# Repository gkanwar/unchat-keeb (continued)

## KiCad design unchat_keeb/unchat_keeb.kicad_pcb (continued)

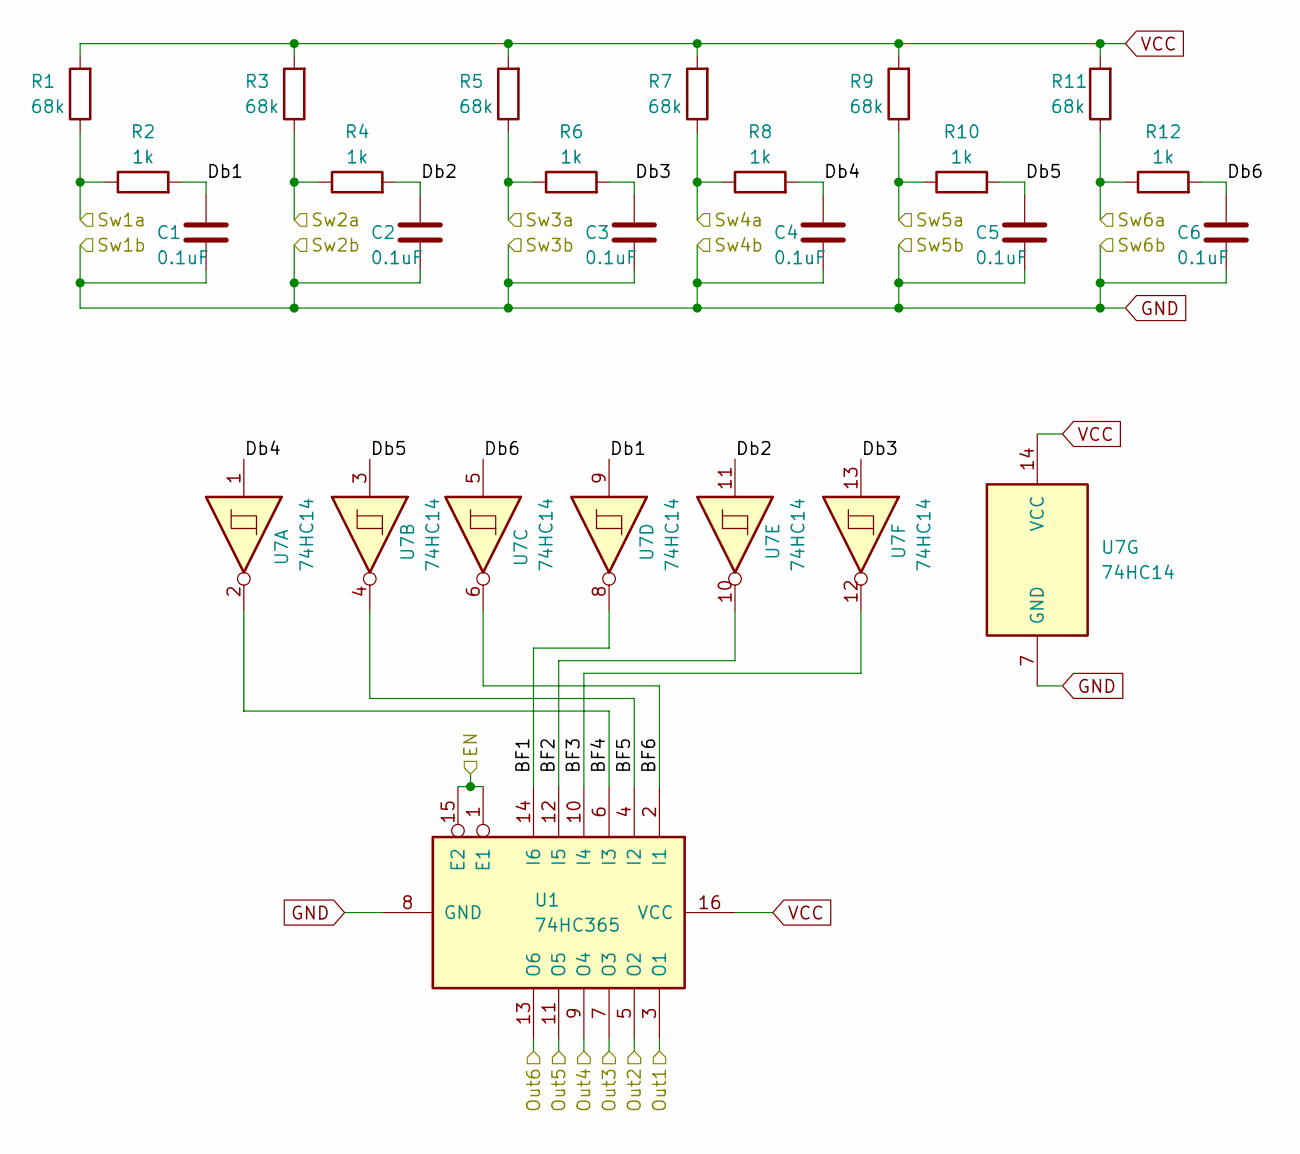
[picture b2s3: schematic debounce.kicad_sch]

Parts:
C1, C2, C3, C4, C5, C6: 0.1uF; C_0805_2012Metric
R1, R3, R5, R7, R9, R11: 68k; R_0805_2012Metric
R2, R4, R6, R8, R10, R12: 1k; R_0805_2012Metric
U1: 74HC365; TSSOP-16_4.4x5mm_P0.65mm
U7: 74HC14; TSSOP-14_4.4x5mm_P0.65mm

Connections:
/BUS1: U1.3 (O1); also elsewhere on the board
/BUS2: U1.5 (O2); also elsewhere on the board
/BUS3: U1.7 (O3); also elsewhere on the board
/BUS4: U1.9 (O4); also elsewhere on the board
/BUS5: U1.11 (O5); also elsewhere on the board
/BUS6: U1.13 (O6); also elsewhere on the board
/Left Debounce 1-6/BF1: U1.14 (I6), U7.8
/Left Debounce 1-6/BF2: U1.12 (I5), U7.10
/Left Debounce 1-6/BF3: U1.10 (I4), U7.12
/Left Debounce 1-6/BF4: U1.6 (I3), U7.2
/Left Debounce 1-6/BF5: U1.4 (I2), U7.4
/Left Debounce 1-6/BF6: U1.2 (I1), U7.6
/Left Debounce 1-6/Db1: C1.1, R2.2, U7.9
/Left Debounce 1-6/Db2: C2.1, R4.2, U7.11
/Left Debounce 1-6/Db4: C4.1, R8.2, U7.1
/Left Debounce 1-6/Db5: C5.1, R10.2, U7.3
/Left Debounce 1-6/Db6: C6.1, R12.2, U7.5
/S1a: R1.1, R2.1; also elsewhere on the board
/S2a: R3.1, R4.1; also elsewhere on the board
/S3a: R5.1, R6.1; also elsewhere on the board
/S4a: R7.1, R8.1; also elsewhere on the board
/S5a: R9.1, R10.1; also elsewhere on the board
/S6a: R11.1, R12.1; also elsewhere on the board
GND: C1.2, C2.2, C3.2, C4.2, C5.2, C6.2, U1.8 (GND), U7.7 (GND); also elsewhere on the board
U1_EN: U1.1 (E1), U1.15 (E2); also elsewhere on the board

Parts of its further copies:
C7, C8, C9, C10, C11, C12, C13, C14, C15, C16, C17, C18, C19, C20, C21, C22, C23, C24, C25, C26, C27, C28, C29, C30, C31, C32, C33, C34, C35, C36, C37, C38, C39, C40, C41, C42: 0.1uF; C_0805_2012Metric
R13, R15, R17, R19, R21, R23, R25, R27, R29, R31, R33, R35, R37, R39, R41, R43, R45, R47, R49, R51, R53, R55, R57, R59, R61, R63, R65, R67, R69, R71, R117, R118, R119, R120, R121, R122: 68k; R_0805_2012Metric
R14, R16, R18, R20, R22, R24, R26, R28, R30, R32, R34, R36, R38, R40, R42, R44, R46, R48, R50, R52, R54, R56, R58, R60, R62, R64, R66, R68, R70, R72, R123, R124, R125, R126, R127, R128: 1k; R_0805_2012Metric
U2, U3, U4, U5, U6, U66: 74HC365; TSSOP-16_4.4x5mm_P0.65mm
U8, U9, U10, U11, U12, U25: 74HC14; TSSOP-14_4.4x5mm_P0.65mm

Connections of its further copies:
/BUS1: U2.3 (O1), U3.3 (O1), U4.3 (O1), U5.3 (O1), U6.3 (O1), U66.3 (O1); also elsewhere on the board
/BUS2: U2.5 (O2), U3.5 (O2), U4.5 (O2), U5.5 (O2), U6.5 (O2), U66.5 (O2); also elsewhere on the board
/BUS3: U2.7 (O3), U3.7 (O3), U4.7 (O3), U5.7 (O3), U6.7 (O3), U66.7 (O3); also elsewhere on the board
/BUS4: U2.9 (O4), U3.9 (O4), U4.9 (O4), U5.9 (O4), U6.9 (O4), U66.9 (O4); also elsewhere on the board
/BUS5: U2.11 (O5), U3.11 (O5), U4.11 (O5), U5.11 (O5), U6.11 (O5), U66.11 (O5); also elsewhere on the board
/BUS6: U2.13 (O6), U3.13 (O6), U4.13 (O6), U5.13 (O6), U6.13 (O6), U66.13 (O6); also elsewhere on the board
/Left Debounce 7-12/BF1: U2.14 (I6), U8.8
/Left Debounce 7-12/BF2: U2.12 (I5), U8.10
/Left Debounce 7-12/BF3: U2.10 (I4), U8.12
/Left Debounce 7-12/BF4: U2.6 (I3), U8.2
/Left Debounce 7-12/BF5: U2.4 (I2), U8.4
/Left Debounce 7-12/BF6: U2.2 (I1), U8.6
/Left Debounce 7-12/Db1: C7.1, R14.2, U8.9
/Left Debounce 7-12/Db2: C8.1, R16.2, U8.11
/Left Debounce 7-12/Db3: C9.1, R18.2, U8.13
/Left Debounce 7-12/Db4: C10.1, R20.2, U8.1
/Left Debounce 7-12/Db5: C11.1, R22.2, U8.3
/Left Debounce 7-12/Db6: C12.1, R24.2, U8.5
/Left Debounce 13-18/BF1: U3.14 (I6), U9.8
/Left Debounce 13-18/BF2: U3.12 (I5), U9.10
/Left Debounce 13-18/BF3: U3.10 (I4), U9.12
/Left Debounce 13-18/BF4: U3.6 (I3), U9.2
/Left Debounce 13-18/BF5: U3.4 (I2), U9.4
/Left Debounce 13-18/BF6: U3.2 (I1), U9.6
/Left Debounce 13-18/Db1: C13.1, R26.2, U9.9
/Left Debounce 13-18/Db2: C14.1, R28.2, U9.11
/Left Debounce 13-18/Db3: C15.1, R30.2, U9.13
/Left Debounce 13-18/Db4: C16.1, R32.2, U9.1
/Left Debounce 13-18/Db5: C17.1, R34.2, U9.3
/Left Debounce 13-18/Db6: C18.1, R36.2, U9.5
/Right Debounce 1-7/BF1: U4.14 (I6), U10.8
/Right Debounce 1-7/BF2: U4.12 (I5), U10.10
/Right Debounce 1-7/BF3: U4.10 (I4), U10.12
/Right Debounce 1-7/BF4: U4.6 (I3), U10.2
/Right Debounce 1-7/BF5: U4.4 (I2), U10.4
/Right Debounce 1-7/BF6: U4.2 (I1), U10.6
/Right Debounce 1-7/Db1: C19.1, R38.2, U10.9
/Right Debounce 1-7/Db2: C20.1, R40.2, U10.11
/Right Debounce 1-7/Db3: C21.1, R42.2, U10.13
/Right Debounce 1-7/Db4: C22.1, R44.2, U10.1
/Right Debounce 1-7/Db5: C23.1, R46.2, U10.3
/Right Debounce 1-7/Db6: C24.1, R48.2, U10.5
/Right Debounce 7-13/BF1: U5.14 (I6), U11.8
/Right Debounce 7-13/BF2: U5.12 (I5), U11.10
/Right Debounce 7-13/BF3: U5.10 (I4), U11.12
/Right Debounce 7-13/BF4: U5.6 (I3), U11.2
/Right Debounce 7-13/BF5: U5.4 (I2), U11.4
/Right Debounce 7-13/BF6: U5.2 (I1), U11.6
/Right Debounce 7-13/Db1: C25.1, R50.2, U11.9
/Right Debounce 7-13/Db2: C26.1, R52.2, U11.11
/Right Debounce 7-13/Db3: C27.1, R54.2, U11.13
/Right Debounce 7-13/Db4: C28.1, R56.2, U11.1
/Right Debounce 7-13/Db5: C29.1, R58.2, U11.3
/Right Debounce 7-13/Db6: C30.1, R60.2, U11.5
/Right Debounce 13-19/BF1: U6.14 (I6), U12.8
/Right Debounce 13-19/BF2: U6.12 (I5), U12.10
/Right Debounce 13-19/BF3: U6.10 (I4), U12.12
/Right Debounce 13-19/BF4: U6.6 (I3), U12.2
/Right Debounce 13-19/BF5: U6.4 (I2), U12.4
/Right Debounce 13-19/BF6: U6.2 (I1), U12.6
/Right Debounce 13-19/Db1: C31.1, R62.2, U12.9
/Right Debounce 13-19/Db2: C32.1, R64.2, U12.11
/Right Debounce 13-19/Db3: C33.1, R66.2, U12.13
/Right Debounce 13-19/Db4: C34.1, R68.2, U12.1
/Right Debounce 13-19/Db5: C35.1, R70.2, U12.3
/Right Debounce 13-19/Db6: C36.1, R72.2, U12.5
/S7a: R13.1, R14.1; also elsewhere on the board
/S8a: R15.1, R16.1; also elsewhere on the board
/S9a: R17.1, R18.1; also elsewhere on the board
/S10a: R19.1, R20.1; also elsewhere on the board
/S11a: R21.1, R22.1; also elsewhere on the board
/S12a: R23.1, R24.1; also elsewhere on the board
/S13a: R25.1, R26.1; also elsewhere on the board
/S14a: R27.1, R28.1; also elsewhere on the board
/S15a: R29.1, R30.1; also elsewhere on the board
/S16a: R31.1, R32.1; also elsewhere on the board
/S17a: R33.1, R34.1; also elsewhere on the board
/S18a: R35.1, R36.1; also elsewhere on the board
/S19a: R117.1, R123.1; also elsewhere on the board
/S20a: R118.1, R124.1; also elsewhere on the board
/S21a: R119.1, R125.1; also elsewhere on the board
/S22a: R37.1, R38.1; also elsewhere on the board
/S23a: R39.1, R40.1; also elsewhere on the board
/S24a: R41.1, R42.1; also elsewhere on the board
/S25a: R43.1, R44.1; also elsewhere on the board
/S26a: R45.1, R46.1; also elsewhere on the board
/S27a: R47.1, R48.1; also elsewhere on the board
/S28a: R49.1, R50.1; also elsewhere on the board
/S29a: R51.1, R52.1; also elsewhere on the board
/S30a: R53.1, R54.1; also elsewhere on the board
/S31a: R55.1, R56.1; also elsewhere on the board
/S32a: R57.1, R58.1; also elsewhere on the board
/S33a: R59.1, R60.1; also elsewhere on the board
/S34a: R61.1, R62.1; also elsewhere on the board
/S35a: R63.1, R64.1; also elsewhere on the board
/S36a: R65.1, R66.1; also elsewhere on the board
/S37a: R67.1, R68.1; also elsewhere on the board
/S38a: R69.1, R70.1; also elsewhere on the board
/S39a: R71.1, R72.1; also elsewhere on the board
/S40a: R120.1, R126.1; also elsewhere on the board
/S41a: R121.1, R127.1; also elsewhere on the board
/S42a: R122.1, R128.1; also elsewhere on the board
/Thumb Debounce/BF1: U25.8, U66.14 (I6)
/Thumb Debounce/BF2: U25.10, U66.12 (I5)
/Thumb Debounce/BF3: U25.12, U66.10 (I4)
/Thumb Debounce/BF4: U25.2, U66.6 (I3)
/Thumb Debounce/BF5: U25.4, U66.4 (I2)
/Thumb Debounce/BF6: U25.6, U66.2 (I1)
/Thumb Debounce/Db1: C37.1, R123.2, U25.9
/Thumb Debounce/Db2: C38.1, R124.2, U25.11
/Thumb Debounce/Db3: C39.1, R125.2, U25.13
/Thumb Debounce/Db4: C40.1, R126.2, U25.1
/Thumb Debounce/Db5: C41.1, R127.2, U25.3
/Thumb Debounce/Db6: C42.1, R128.2, U25.5
GND: C7.2, C8.2, C9.2, C10.2, C11.2, C12.2, C13.2, C14.2, C15.2, C16.2, C17.2, C18.2, C19.2, C20.2, C21.2, C22.2, C23.2, C24.2, C25.2, C26.2, C27.2, C28.2, C29.2, C30.2, C31.2, C32.2, C33.2, C34.2, C35.2, C36.2, C37.2, C38.2, C39.2, C40.2, C41.2, C42.2, U2.8 (GND), U3.8 (GND), U4.8 (GND), U5.8 (GND), U6.8 (GND), U8.7 (GND), U9.7 (GND), U10.7 (GND), U11.7 (GND), U12.7 (GND), U25.7 (GND), U66.8 (GND); also elsewhere on the board
U2_EN: U2.1 (E1), U2.15 (E2); also elsewhere on the board
U3_EN: U3.1 (E1), U3.15 (E2); also elsewhere on the board
U4_EN: U4.1 (E1), U4.15 (E2); also elsewhere on the board
U5_EN: U5.1 (E1), U5.15 (E2); also elsewhere on the board
U6_EN: U6.1 (E1), U6.15 (E2); also elsewhere on the board
U66_EN: U66.1 (E1), U66.15 (E2); also elsewhere on the board

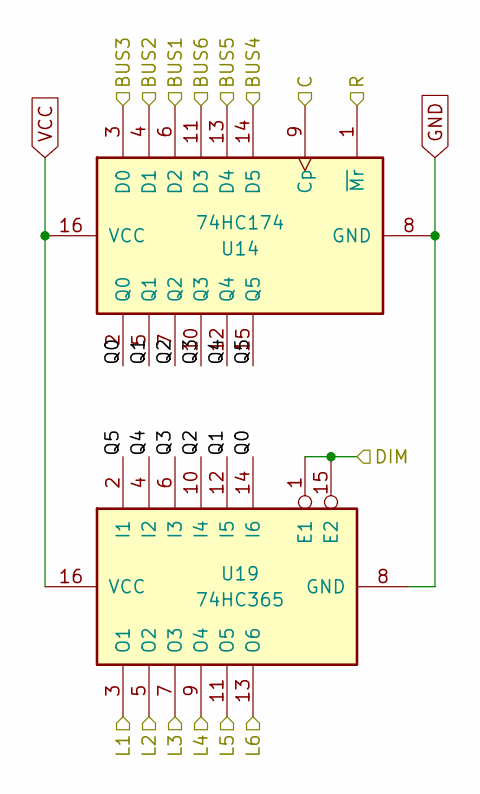
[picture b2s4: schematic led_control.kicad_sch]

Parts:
U14: 74HC174; TSSOP-16_4.4x5mm_P0.65mm
U19: 74HC365; TSSOP-16_4.4x5mm_P0.65mm

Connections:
/BUS1: U14.6 (D2); also elsewhere on the board
/BUS2: U14.4 (D1); also elsewhere on the board
/BUS3: U14.3 (D0); also elsewhere on the board
/BUS4: U14.14 (D5); also elsewhere on the board
/BUS5: U14.13 (D4); also elsewhere on the board
/BUS6: U14.11 (D3); also elsewhere on the board
/LL2: U19.5 (O2); also elsewhere on the board
/LL3: U19.7 (O3); also elsewhere on the board
/LL4: U19.9 (O4); also elsewhere on the board
/LL5: U19.11 (O5); also elsewhere on the board
/LL6: U19.13 (O6); also elsewhere on the board
GND: U14.8 (GND), U19.8 (GND); also elsewhere on the board
LED_DIM: U19.1 (E1), U19.15 (E2); also elsewhere on the board
LED_RST: U14.1 (~Mr); also elsewhere on the board
U14_CLK: U14.9 (Cp); also elsewhere on the board

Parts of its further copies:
U13, U15, U16, U17, U18, U26: 74HC174; TSSOP-16_4.4x5mm_P0.65mm
U20, U21, U22, U23, U24, U27: 74HC365; TSSOP-16_4.4x5mm_P0.65mm

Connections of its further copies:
/BUS1: U13.6 (D2), U15.6 (D2), U16.6 (D2), U17.6 (D2), U18.6 (D2), U26.6 (D2); also elsewhere on the board
/BUS2: U13.4 (D1), U15.4 (D1), U16.4 (D1), U17.4 (D1), U18.4 (D1), U26.4 (D1); also elsewhere on the board
/BUS3: U13.3 (D0), U15.3 (D0), U16.3 (D0), U17.3 (D0), U18.3 (D0), U26.3 (D0); also elsewhere on the board
/BUS4: U13.14 (D5), U15.14 (D5), U16.14 (D5), U17.14 (D5), U18.14 (D5), U26.14 (D5); also elsewhere on the board
/BUS5: U13.13 (D4), U15.13 (D4), U16.13 (D4), U17.13 (D4), U18.13 (D4), U26.13 (D4); also elsewhere on the board
/BUS6: U13.11 (D3), U15.11 (D3), U16.11 (D3), U17.11 (D3), U18.11 (D3), U26.11 (D3); also elsewhere on the board
/LL7: U20.3 (O1); also elsewhere on the board
/LL8: U20.5 (O2); also elsewhere on the board
/LL9: U20.7 (O3); also elsewhere on the board
/LL10: U20.9 (O4); also elsewhere on the board
/LL11: U20.11 (O5); also elsewhere on the board
/LL12: U20.13 (O6); also elsewhere on the board
/LL13: U21.3 (O1); also elsewhere on the board
/LL14: U21.5 (O2); also elsewhere on the board
/LL15: U21.7 (O3); also elsewhere on the board
/LL16: U21.9 (O4); also elsewhere on the board
/LL17: U21.11 (O5); also elsewhere on the board
/LL18: U21.13 (O6); also elsewhere on the board
/LL19: U27.3 (O1); also elsewhere on the board
/LL20: U27.5 (O2); also elsewhere on the board
/LL21: U27.7 (O3); also elsewhere on the board
/LR1: U22.3 (O1); also elsewhere on the board
/LR2: U22.5 (O2); also elsewhere on the board
/LR3: U22.7 (O3); also elsewhere on the board
/LR4: U22.9 (O4); also elsewhere on the board
/LR5: U22.11 (O5); also elsewhere on the board
/LR6: U22.13 (O6); also elsewhere on the board
/LR7: U23.3 (O1); also elsewhere on the board
/LR8: U23.5 (O2); also elsewhere on the board
/LR9: U23.7 (O3); also elsewhere on the board
/LR10: U23.9 (O4); also elsewhere on the board
/LR11: U23.11 (O5); also elsewhere on the board
/LR12: U23.13 (O6); also elsewhere on the board
/LR13: U24.3 (O1); also elsewhere on the board
/LR14: U24.5 (O2); also elsewhere on the board
/LR15: U24.7 (O3); also elsewhere on the board
/LR16: U24.9 (O4); also elsewhere on the board
/LR17: U24.11 (O5); also elsewhere on the board
/LR18: U24.13 (O6); also elsewhere on the board
/LR19: U27.9 (O4); also elsewhere on the board
/LR20: U27.11 (O5); also elsewhere on the board
/LR21: U27.13 (O6); also elsewhere on the board
/Left LED Control 13-18/Q0: U15.2 (Q0), U21.14 (I6)
/Left LED Control 13-18/Q1: U15.5 (Q1), U21.12 (I5)
/Left LED Control 13-18/Q2: U15.7 (Q2), U21.10 (I4)
/Left LED Control 13-18/Q3: U15.10 (Q3), U21.6 (I3)
/Left LED Control 13-18/Q4: U15.12 (Q4), U21.4 (I2)
/Left LED Control 13-18/Q5: U15.15 (Q5), U21.2 (I1)
/Right LED Control 1-6/Q0: U16.2 (Q0), U22.14 (I6)
/Right LED Control 1-6/Q1: U16.5 (Q1), U22.12 (I5)
/Right LED Control 1-6/Q2: U16.7 (Q2), U22.10 (I4)
/Right LED Control 1-6/Q3: U16.10 (Q3), U22.6 (I3)
/Right LED Control 1-6/Q4: U16.12 (Q4), U22.4 (I2)
/Right LED Control 1-6/Q5: U16.15 (Q5), U22.2 (I1)
/Right LED Control 7-12/Q0: U17.2 (Q0), U23.14 (I6)
/Right LED Control 7-12/Q1: U17.5 (Q1), U23.12 (I5)
/Right LED Control 7-12/Q2: U17.7 (Q2), U23.10 (I4)
/Right LED Control 7-12/Q3: U17.10 (Q3), U23.6 (I3)
/Right LED Control 7-12/Q4: U17.12 (Q4), U23.4 (I2)
/Right LED Control 7-12/Q5: U17.15 (Q5), U23.2 (I1)
/Right LED Control 13-18/Q0: U18.2 (Q0), U24.14 (I6)
/Right LED Control 13-18/Q1: U18.5 (Q1), U24.12 (I5)
/Right LED Control 13-18/Q2: U18.7 (Q2), U24.10 (I4)
/Right LED Control 13-18/Q3: U18.10 (Q3), U24.6 (I3)
/Right LED Control 13-18/Q4: U18.12 (Q4), U24.4 (I2)
/Right LED Control 13-18/Q5: U18.15 (Q5), U24.2 (I1)
/Thumb LED Control/Q0: U26.2 (Q0), U27.14 (I6)
/Thumb LED Control/Q1: U26.5 (Q1), U27.12 (I5)
/Thumb LED Control/Q2: U26.7 (Q2), U27.10 (I4)
/Thumb LED Control/Q3: U26.10 (Q3), U27.6 (I3)
/Thumb LED Control/Q4: U26.12 (Q4), U27.4 (I2)
/Thumb LED Control/Q5: U26.15 (Q5), U27.2 (I1)
GND: U13.8 (GND), U15.8 (GND), U16.8 (GND), U17.8 (GND), U18.8 (GND), U20.8 (GND), U21.8 (GND), U22.8 (GND), U23.8 (GND), U24.8 (GND), U26.8 (GND), U27.8 (GND); also elsewhere on the board
LED_DIM: U20.1 (E1), U20.15 (E2), U21.1 (E1), U21.15 (E2), U22.1 (E1), U22.15 (E2), U23.1 (E1), U23.15 (E2), U24.1 (E1), U24.15 (E2), U27.1 (E1), U27.15 (E2); also elsewhere on the board
LED_RST: U13.1 (~Mr), U15.1 (~Mr), U16.1 (~Mr), U17.1 (~Mr), U18.1 (~Mr), U26.1 (~Mr); also elsewhere on the board
U13_CLK: U13.9 (Cp); also elsewhere on the board
U15_CLK: U15.9 (Cp); also elsewhere on the board
U16_CLK: U16.9 (Cp); also elsewhere on the board
U17_CLK: U17.9 (Cp); also elsewhere on the board
U18_CLK: U18.9 (Cp); also elsewhere on the board
U26_CLK: U26.9 (Cp); also elsewhere on the board

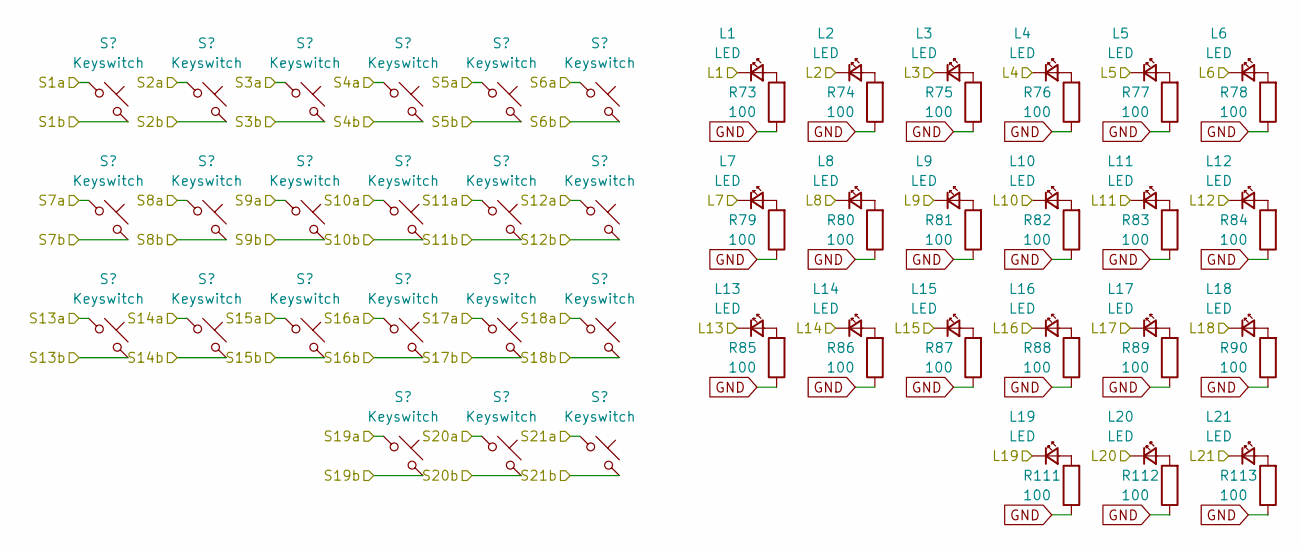
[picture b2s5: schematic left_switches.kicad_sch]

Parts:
L1, L2, L3, L4, L5, L6, L7, L8, L9, L10, L11, L12, L13, L14, L15, L16, L17, L18, L19, L20, L21: LED; LED_0603_1608Metric
R73, R74, R75, R76, R77, R78, R79, R80, R81, R82, R83, R84, R85, R86, R87, R88, R89, R90, R111, R112, R113: 100; R_0805_2012Metric
S1, S2, S3, S4, S5, S6, S7, S8, S9, S10, S11, S12, S13, S14, S15, S16, S17, S18, S19: Keyswitch; Choc_V1_LED_1.00u
S20, S21: Keyswitch; Choc_V1_LED_1.50u_90deg

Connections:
/LL2: L2.1 (K); also elsewhere on the board
/LL3: L3.1 (K); also elsewhere on the board
/LL4: L4.1 (K); also elsewhere on the board
/LL5: L5.1 (K); also elsewhere on the board
/LL6: L6.1 (K); also elsewhere on the board
/LL7: L7.1 (K); also elsewhere on the board
/LL8: L8.1 (K); also elsewhere on the board
/LL9: L9.1 (K); also elsewhere on the board
/LL10: L10.1 (K); also elsewhere on the board
/LL11: L11.1 (K); also elsewhere on the board
/LL12: L12.1 (K); also elsewhere on the board
/LL13: L13.1 (K); also elsewhere on the board
/LL14: L14.1 (K); also elsewhere on the board
/LL15: L15.1 (K); also elsewhere on the board
/LL16: L16.1 (K); also elsewhere on the board
/LL17: L17.1 (K); also elsewhere on the board
/LL18: L18.1 (K); also elsewhere on the board
/LL19: L19.1 (K); also elsewhere on the board
/LL20: L20.1 (K); also elsewhere on the board
/LL21: L21.1 (K); also elsewhere on the board
/S1a: S1.1; also elsewhere on the board
/S2a: S2.1; also elsewhere on the board
/S3a: S3.1; also elsewhere on the board
/S4a: S4.1; also elsewhere on the board
/S5a: S5.1; also elsewhere on the board
/S6a: S6.1; also elsewhere on the board
/S7a: S7.1; also elsewhere on the board
/S8a: S8.1; also elsewhere on the board
/S9a: S9.1; also elsewhere on the board
/S10a: S10.1; also elsewhere on the board
/S11a: S11.1; also elsewhere on the board
/S12a: S12.1; also elsewhere on the board
/S13a: S13.1; also elsewhere on the board
/S14a: S14.1; also elsewhere on the board
/S15a: S15.1; also elsewhere on the board
/S16a: S16.1; also elsewhere on the board
/S17a: S17.1; also elsewhere on the board
/S18a: S18.1; also elsewhere on the board
/S19a: S19.1; also elsewhere on the board
/S20a: S20.1; also elsewhere on the board
/S21a: S21.1; also elsewhere on the board
GND: R73.1, R74.1, R75.1, R76.1, R77.1, R78.1, R79.1, R80.1, R81.1, R82.1, R83.1, R84.1, R85.1, R86.1, R87.1, R88.1, R89.1, R90.1, R111.1, R112.1, R113.1, S1.2, S2.2, S3.2, S4.2, S5.2, S6.2, S7.2, S8.2, S9.2, S10.2, S11.2, S12.2, S13.2, S14.2, S15.2, S16.2, S17.2, S18.2, S19.2, S20.2, S21.2; also elsewhere on the board
unnamed: L1.2 (A), R73.2
unnamed: L2.2 (A), R74.2
unnamed: L3.2 (A), R75.2
unnamed: L4.2 (A), R76.2
unnamed: L5.2 (A), R77.2
unnamed: L6.2 (A), R78.2
unnamed: L7.2 (A), R79.2
unnamed: L8.2 (A), R80.2
unnamed: L9.2 (A), R81.2
unnamed: L10.2 (A), R82.2
unnamed: L11.2 (A), R83.2
unnamed: L12.2 (A), R84.2
unnamed: L13.2 (A), R85.2
unnamed: L14.2 (A), R86.2
unnamed: L15.2 (A), R87.2
unnamed: L16.2 (A), R88.2
unnamed: L17.2 (A), R89.2
unnamed: L18.2 (A), R90.2
unnamed: L19.2 (A), R111.2
unnamed: L20.2 (A), R112.2
unnamed: L21.2 (A), R113.2

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
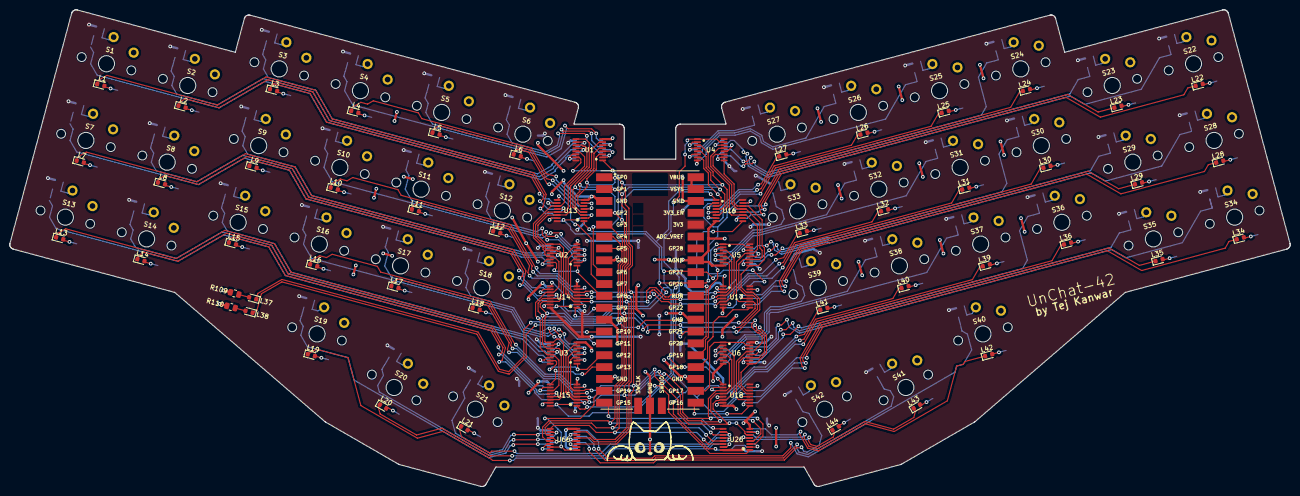
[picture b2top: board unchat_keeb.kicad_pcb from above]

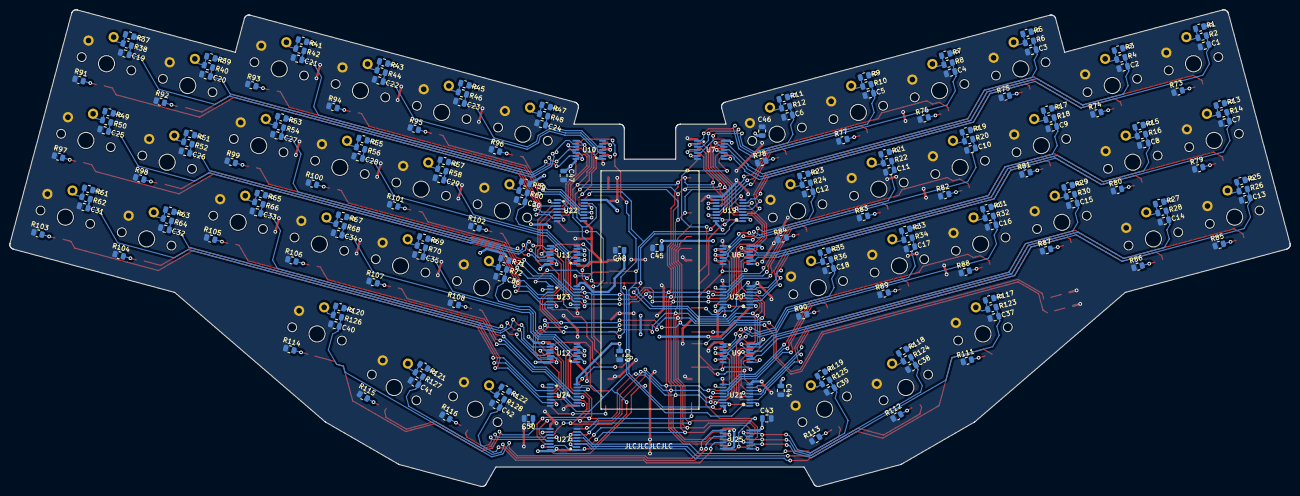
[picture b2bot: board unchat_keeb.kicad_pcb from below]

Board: 2 copper layers, 274.0 x 102.0 mm, 293 parts (190 on the bottom side), 281 nets.

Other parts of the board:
L39, L40, L41, L42, L43, L44: LED; LED_0603_1608Metric
R114, R115, R116: 100; R_0805_2012Metric
S37, S38, S39, S40: Keyswitch; Choc_V1_LED_1.00u
S41, S42: Keyswitch; Choc_V1_LED_1.50u_90deg

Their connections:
/LR16: L39.1 (K); also elsewhere on the board
/LR17: L40.1 (K); also elsewhere on the board
/LR18: L41.1 (K); also elsewhere on the board
/LR19: L42.1 (K); also elsewhere on the board
/LR20: L43.1 (K); also elsewhere on the board
/LR21: L44.1 (K); also elsewhere on the board
/S37a: S37.1; also elsewhere on the board
/S38a: S38.1; also elsewhere on the board
/S39a: S39.1; also elsewhere on the board
/S40a: S40.1; also elsewhere on the board
/S41a: S41.1; also elsewhere on the board
/S42a: S42.1; also elsewhere on the board
GND: R114.1, R115.1, R116.1, S37.2, S38.2, S39.2, S40.2, S41.2, S42.2; also elsewhere on the board
unnamed 243: L39.2 (A); also elsewhere on the board
unnamed 244: L40.2 (A); also elsewhere on the board
unnamed 245: L41.2 (A); also elsewhere on the board
unnamed: L42.2 (A), R114.2
unnamed: L43.2 (A), R115.2
unnamed: L44.2 (A), R116.2

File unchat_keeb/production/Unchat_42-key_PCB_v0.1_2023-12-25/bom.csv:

Designator,Footprint,Quantity,Value,LCSC Part #
"C1, C10, C11, C12, C13, C14, C15, C16, C17, C18, C19, C2, C20, C21, C22, C23, C24, C25, C26, C27, C28, C29, C3, C30, C31, C32, C33, C34, C35, C36, C37, C38, C39, C4, C40, C41, C42, C43, C44, C45, C46, C47, C48, C49, C5, C50, C6, C7, C8, C9",0805,50,0.1uF,
"L1, L10, L11, L12, L13, L14, L15, L16, L17, L18, L19, L2, L20, L21, L22, L23, L24, L25, L26, L27, L28, L29, L3, L30, L31, L32, L33, L34, L35, L36, L37, L38, L39, L4, L40, L41, L42, L43, L44, L5, L6, L7, L8, L9",0603,44,LED,
"R1, R11, R117, R118, R119, R120, R121, R122, R13, R15, R17, R19, R21, R23, R25, R27, R29, R3, R31, R33, R35, R37, R39, R41, R43, R45, R47, R49, R5, R51, R53, R55, R57, R59, R61, R63, R65, R67, R69, R7, R71, R9",0805,42,68k,
"R10, R12, R123, R124, R125, R126, R127, R128, R14, R16, R18, R2, R20, R22, R24, R26, R28, R30, R32, R34, R36, R38, R4, R40, R42, R44, R46, R48, R50, R52, R54, R56, R58, R6, R60, R62, R64, R66, R68, R70, R72, R8",0805,42,1k,
"R100, R101, R102, R103, R104, R105, R106, R107, R108, R109, R110, R111, R112, R113, R114, R115, R116, R73, R74, R75, R76, R77, R78, R79, R80, R81, R82, R83, R84, R85, R86, R87, R88, R89, R90, R91, R92, R93, R94, R95, R96, R97, R98, R99",0805,44,100,
"S1, S10, S11, S12, S13, S14, S15, S16, S17, S18, S19, S2, S22, S23, S24, S25, S26, S27, S28, S29, S3, S30, S31, S32, S33, S34, S35, S36, S37, S38, S39, S4, S40, S5, S6, S7, S8, S9",Choc_V1_LED_1.00u,38,Keyswitch,
"S20, S21, S41, S42",Choc_V1_LED_1.50u_90deg,4,Keyswitch,
"U1, U19, U2, U20, U21, U22, U23, U24, U27, U3, U4, U5, U6, U66",TSSOP-16_4.4x5mm_P0.65mm,14,74HC365,
"U10, U11, U12, U25, U7, U8, U9",TSSOP-14_4.4x5mm_P0.65mm,7,74HC14,
"U13, U14, U15, U16, U17, U18, U26",TSSOP-16_4.4x5mm_P0.65mm,7,74HC174,
U99,Raspberry_Pi_Pico_SMD,1,Raspberry_Pi_Pico,

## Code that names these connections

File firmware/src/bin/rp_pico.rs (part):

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  UserPins {
    led: GpioOut::new(pins.led),
    general_pins: [
      GpioIn::new(pins.gpio0),
      GpioIn::new(pins.gpio1),
      GpioIn::new(pins.gpio2),
      GpioIn::new(pins.gpio3),
      GpioIn::new(pins.gpio4),
      GpioIn::new(pins.gpio5),
      GpioIn::new(pins.gpio6),
      GpioIn::new(pins.gpio7),
      GpioIn::new(pins.gpio8),
      GpioIn::new(pins.gpio9),
      GpioIn::new(pins.gpio10),
      GpioIn::new(pins.gpio11),
      GpioIn::new(pins.gpio12),
      GpioIn::new(pins.gpio13),
      GpioIn::new(pins.gpio14),
      GpioIn::new(pins.gpio15),
      GpioIn::new(pins.gpio16),
      GpioIn::new(pins.gpio17),
      GpioIn::new(pins.gpio18),
      GpioIn::new(pins.gpio19),
      GpioIn::new(pins.gpio20),
      GpioIn::new(pins.gpio21),
      GpioIn::new(pins.gpio22),
      GpioIn::new(pins.gpio26),
      GpioIn::new(pins.gpio27),
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
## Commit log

2023-12-10 Initialize repo with basic PCB design and libraries
2023-12-17 Add extra columns, updating to 42-key design
2023-12-17 Add RP2040 datasheet
2023-12-22 Add dxf layout and finish half keyboard pbc layout
2023-12-23 Position right switches, update dxf dims, and fix symb lib paths
2023-12-24 Route remaining components, except VCC and GND
2023-12-24 Add custom footprints with fixed courtyards
2023-12-24 Finalize the board
2023-12-25 Add bus pullups, still need to route 'em
2023-12-25 Remove pullups, as RPi GPIOs are pulled by default
2023-12-25 Add thermal relief cuts
2023-12-25 Fix 1.5u keycap orientation
2023-12-26 Add JLCPCB production files
    v0.2: last-minute rotation to thumb switches
2023-12-26 Init embedded rust project for firmware
2023-12-27 Attempt to use ZMK dts format
    Doesn't seem particularly well-suited to this application. Far too general
    and relies heavily on preprocessor macros which do not work across FFI. The
    unchat keeb firmware should be more targeted anyway.
2023-12-27 firmware: Add layout parsing from JSON
2023-12-27 firmware: Implement more complete layout deser
2023-12-28 firmware: Implement basic IO bus
2023-12-28 firmware: Implement basic sketch of all pieces
2023-12-28 board: Add rendered schematics for easy access
2023-12-28 keymap: Fix accidental base transparent key
2024-01-01 firmware: Add basic USB keyboard device stack
2024-01-01 docs: Add USB HID specs
2024-01-02 firmware: Playing with usb latency
    Helps to not spam packets, only update if state is changed.
2024-01-03 docs: Add PCB design guidelines
2024-01-06 firmware: Add test loop
2024-01-06 firmware: Partial implementation of vkeyboard
2024-01-09 firmware: Implement simple switch+led test
    Hardware appears to work!
2024-01-09 firmware: Implement bus write lock
2024-01-09 firmware: Tie everything together in rp_pico
    Debugging still required!
2024-01-09 firmware: Fix basic problems
    It (mostly) works!!
2024-01-10 firmware: Add rp2040-e5 feature flag
    My boards use RP2040-B1 which is affected by this erratum.
2024-01-10 firmware: Add delays for timing on switch reads
2024-01-10 firmware: Fix updated early-return bug
    Keys actually type extremely reliably now!!! Amazing.
2024-01-11 firmware: Fix USB poll rate and packet spam
2024-01-11 firmware: Implement basic layers
2024-01-13 Adds Enter to keymap
2024-02-25 firmware: Clean up a few things
2024-02-25 firmware: Fix padding bug and osx quirks
2024-11-17 Unchat-40: Kicad project and CAD design for top/bottom plates
2024-11-25 firmware: osx expts
2024-11-30 firmware v2: Basic impl with most core functionality
    * Scanning all 16 analog registers with associative map to switch matrix
    * Hysteresis for key up/down triggers
    * Neopixel control
    * Serial over USB with logging, including on panics
2024-12-01 firmware v2: Draft 40-key keymap
2024-12-01 readme: Added with many images and a snippet of the timelapse
2024-12-25 firmware v2: Fix serial rendering bug, clean up layout and usb impl
2024-12-25 firmware v2: tweak HE sensitivity
